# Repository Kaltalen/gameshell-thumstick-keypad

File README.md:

# Gameshell Thumstick Keypad

A Project to add Thumbsticks to a Clockwork Gameshell.

## Getting Started

Work In Progress

This is somthing ive been playing around with.

Uses a Arduino Micro Pro.

Got it upto the stage where it was detected by windows as a gamepad and all buttons/thumsticks were detected correctly.

Yet to actually incorperate it into my gameshell. 

Includes:
- Arduino Sketch
- Eagle files for PCB
- STL files for printable case

TODO:
- Add arduino to PCB
- (optional) change resistors to surface mount
- Integrate case into new Gameshell case
- (optional) chagne thumbsticks for FJ08k-s
- use existing keypad connector?

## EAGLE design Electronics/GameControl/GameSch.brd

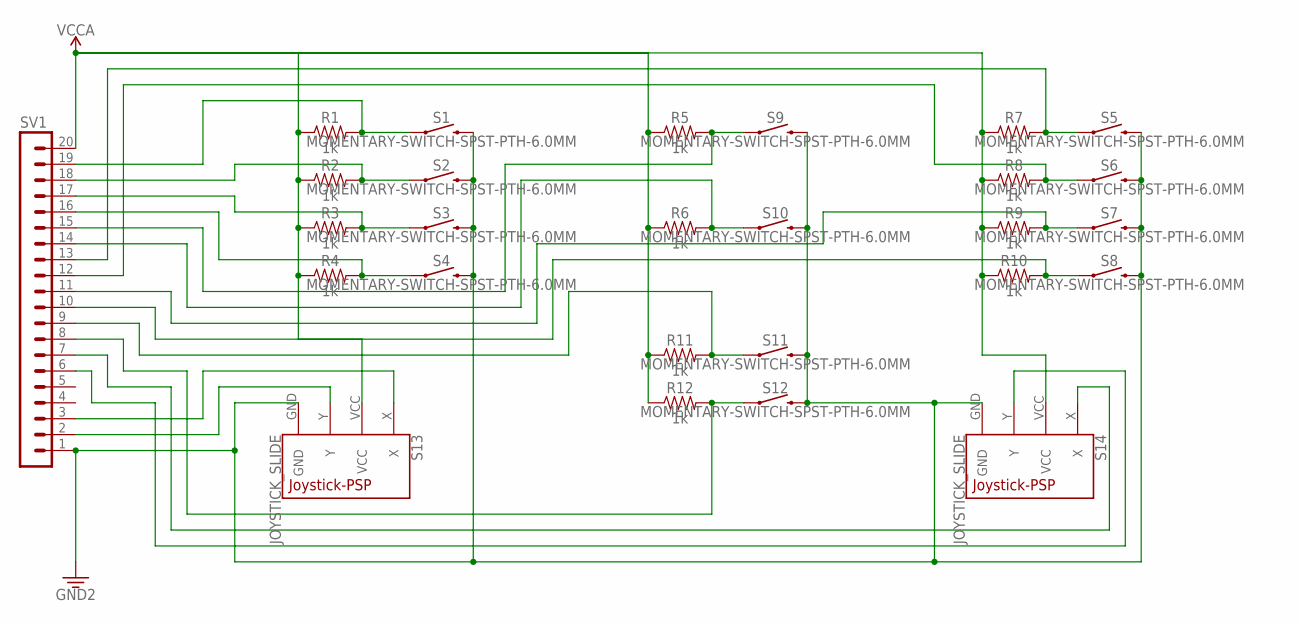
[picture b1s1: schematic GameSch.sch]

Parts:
R1, R2, R3, R4, R5, R6, R7, R8, R9, R10, R11, R12: 1k; AXIAL-0.3
S1, S2, S3, S4, S5, S6, S7, S8, S9, S10, S11, S12: MOMENTARY-SWITCH-SPST-PTH-6.0MM; TACTILE_SWITCH_PTH_6.0MM
S13, S14: JOYSTICK_SLIDE; JOYSTICK-PSP1000
SV1: MA20-1

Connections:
3.3V: S1.3 (2), S2.3 (2), S3.3 (2), S4.3 (2), S5.3 (2), S6.3 (2), S7.3 (2), S8.3 (2), S9.3 (2), S10.3 (2), S11.3 (2), S12.3 (2), S13.GND, S14.GND, SV1.1
unnamed: R1.P$2 (2), S1.1, SV1.19
unnamed: R2.P$2 (2), S2.1, SV1.18
unnamed: R3.P$2 (2), S3.1, SV1.17
unnamed: R4.P$2 (2), S4.1, SV1.16
unnamed: R5.P$2 (2), S9.1, SV1.15
unnamed: R6.P$2 (2), S10.1, SV1.14
unnamed: R11.P$2 (2), S11.1, SV1.9
unnamed: R12.P$2 (2), S12.1, SV1.8
unnamed: R7.P$2 (2), S5.1, SV1.13
unnamed: R8.P$2 (2), S6.1, SV1.12
unnamed: R9.P$2 (2), S7.1, SV1.11
unnamed: R10.P$2 (2), S8.1, SV1.10
unnamed: S14.X, SV1.7
unnamed: S14.Y, SV1.6
unnamed: S13.Y, SV1.2
unnamed: S13.X, SV1.3
VCCA: R1.P$1 (1), R2.P$1 (1), R3.P$1 (1), R4.P$1 (1), R5.P$1 (1), R6.P$1 (1), R7.P$1 (1), R8.P$1 (1), R9.P$1 (1), R10.P$1 (1), R11.P$1 (1), R12.P$1 (1), S13.VCC, S14.VCC, SV1.20

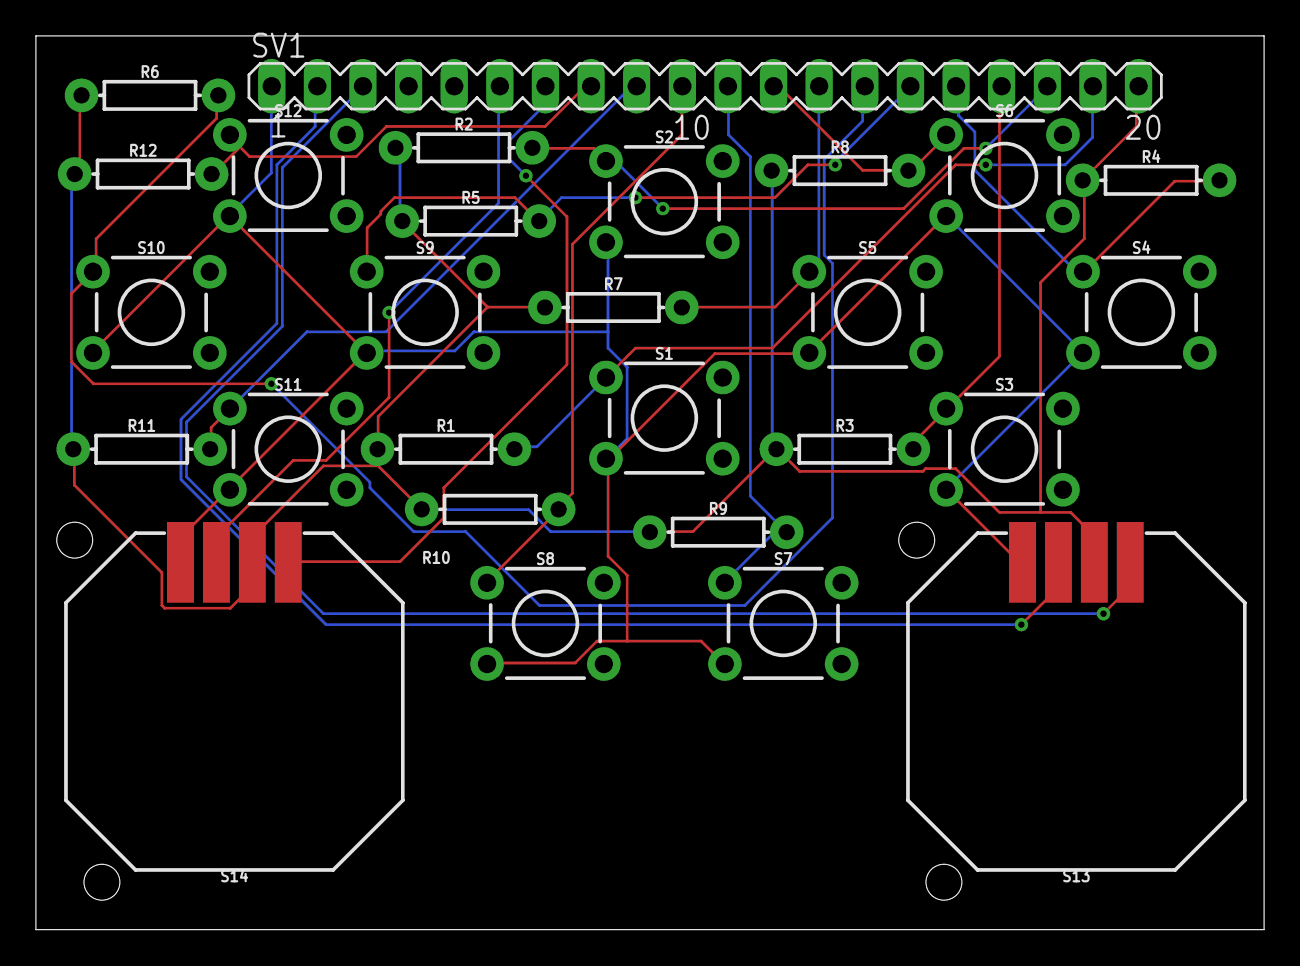
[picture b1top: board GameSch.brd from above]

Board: 2 copper layers, 68.4 x 49.8 mm, 27 parts (0 on the bottom side), 18 nets.

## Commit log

2019-09-03 Added Content
2020-09-28 Add TODO

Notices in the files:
parts and their libraries:
SparkFun-Resistors: Licensing: Creative Commons ShareAlike 4.0 International - https://creativecommons.org/licenses/by-sa/4.0
